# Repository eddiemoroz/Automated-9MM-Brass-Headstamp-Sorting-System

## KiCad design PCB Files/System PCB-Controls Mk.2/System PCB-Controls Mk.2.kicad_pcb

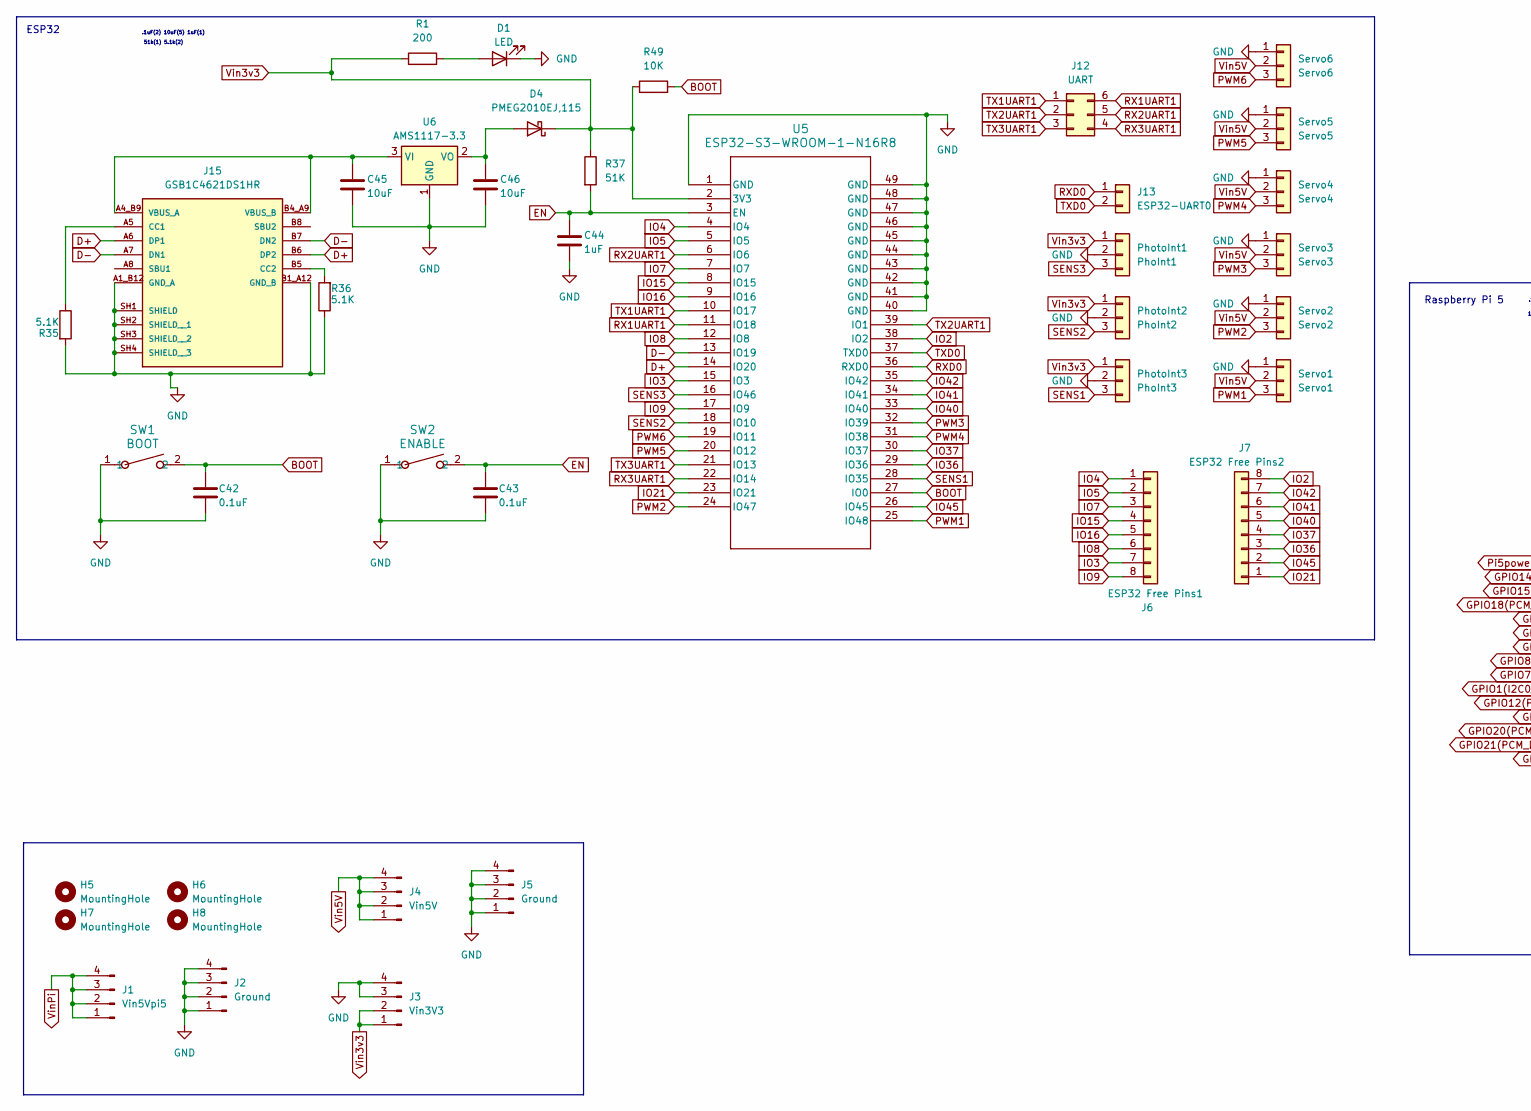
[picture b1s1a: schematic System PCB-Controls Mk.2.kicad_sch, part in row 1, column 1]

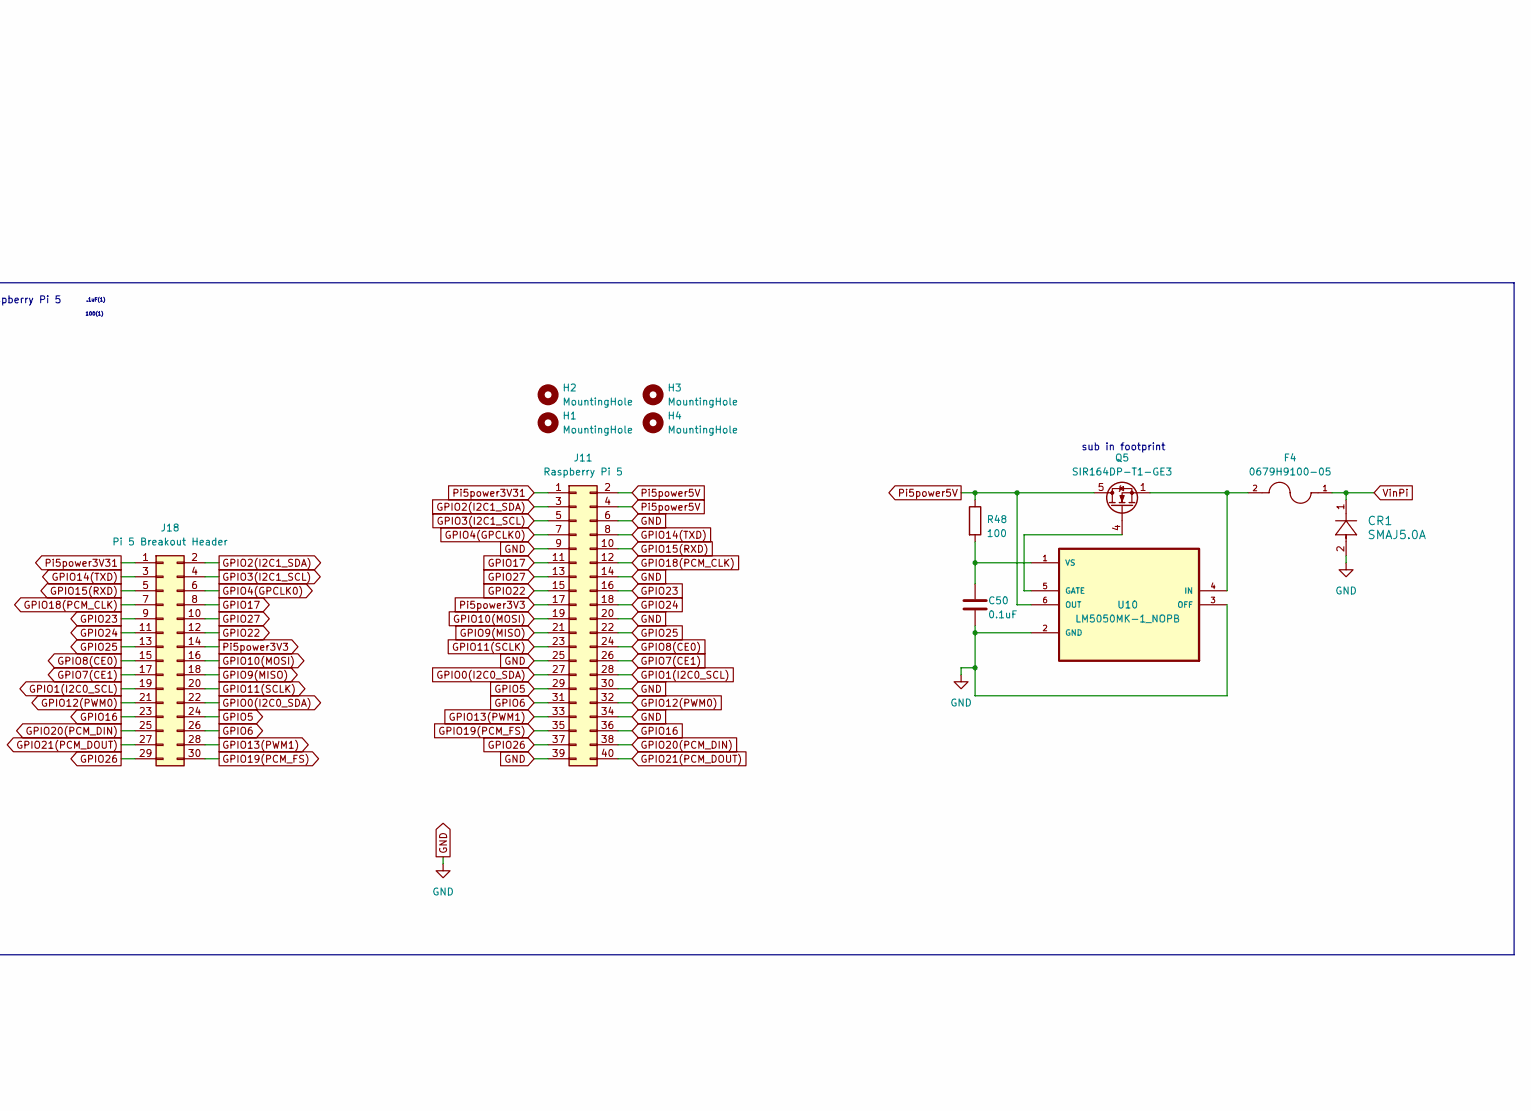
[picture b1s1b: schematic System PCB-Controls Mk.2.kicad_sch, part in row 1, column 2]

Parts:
C42, C43, C50: 0.1uF; C_0805_2012Metric_Pad1.18x1.45mm_HandSolder
C44: 1uF; C_0603_1608Metric_Pad1.08x0.95mm_HandSolder
C45, C46: 10uF; C_1206_3216Metric_Pad1.33x1.80mm_HandSolder
CR1: SMAJ5.0A; SMA5.0A
D1: LED; R_1206_3216Metric_Pad1.30x1.75mm_HandSolder
D4: PMEG2010EJ,115; D_SOD-323F
F4: 0679H9100-05; FUSC6125X279N; PARTREV 0679H Apr2019
H1, H2, H3, H4: MountingHole; MountingHole_2.7mm_M2.5
H5, H6, H7, H8: MountingHole; MountingHole_3.2mm_M3
J1: Vin5Vpi5; FanPinHeader_1x04_P2.54mm_Vertical
J2, J5: Ground; FanPinHeader_1x04_P2.54mm_Vertical
J3: Vin3V3; FanPinHeader_1x04_P2.54mm_Vertical
J4: Vin5V; FanPinHeader_1x04_P2.54mm_Vertical
J6: ESP32 Free Pins1; PinSocket_1x08_P2.54mm_Vertical
J7: ESP32 Free Pins2; PinSocket_1x08_P2.54mm_Vertical
J11: Raspberry Pi 5; PinSocket_2x20_P2.54mm_Vertical
J12: UART; PinSocket_2x03_P2.54mm_Vertical
J13: ESP32-UART0; PinSocket_1x02_P2.54mm_Vertical
J15: GSB1C4621DS1HR; AMPHENOL_GSB1C4621DS1HR; PARTREV AX1
J18: Pi 5 Breakout Header; PinHeader_2x15_P2.54mm_Vertical
PhotoInt1: PhoInt1; FanPinHeader_1x03_P2.54mm_Vertical
PhotoInt2: PhoInt2; FanPinHeader_1x03_P2.54mm_Vertical
PhotoInt3: PhoInt3; FanPinHeader_1x03_P2.54mm_Vertical
Q5: SIR164DP-T1-GE3; PowerPAK_SO-8_Single
R1: 200; R_1206_3216Metric_Pad1.30x1.75mm_HandSolder
R35, R36: 5.1K; R_1206_3216Metric_Pad1.30x1.75mm_HandSolder
R37: 51K; R_1206_3216Metric_Pad1.30x1.75mm_HandSolder
R48: 100; R_1206_3216Metric_Pad1.30x1.75mm_HandSolder
R49: 10K; R_1206_3216Metric_Pad1.30x1.75mm_HandSolder
SW1: BOOT; SW_PTS636_CNK
SW2: ENABLE; SW_PTS636_CNK
Servo1: Servo1; PinSocket_1x03_P2.54mm_Vertical
Servo2: Servo2; PinSocket_1x03_P2.54mm_Vertical
Servo3: Servo3; PinSocket_1x03_P2.54mm_Vertical
Servo4: Servo4; PinSocket_1x03_P2.54mm_Vertical
Servo5: Servo5; PinSocket_1x03_P2.54mm_Vertical
Servo6: Servo6; PinSocket_1x03_P2.54mm_Vertical
U5: ESP32-S3-WROOM-1-N16R8; ESP32-S3-WROOM-1_EXP
U6: AMS1117-3.3; SOT-223-3_TabPin2
U10: LM5050MK-1_NOPB; LM5050MK-1NOPB

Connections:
BOOT: C42.1, R49.2, SW1.2, U5.27 (IO0)
D+: J15.A6 (DP1), J15.B6 (DP2), U5.14 (IO20)
D-: J15.A7 (DN1), J15.B7 (DN2), U5.13 (IO19)
EN: C43.1, C44.1, R37.2, SW2.2, U5.3 (EN)
GND: C42.2, C43.2, C44.2, C45.2, C46.2, C50.2, CR1.2, D1.1 (K), J2.1, J2.2, J2.3, J2.4, J3.3, J3.4, J5.1, J5.2, J5.3, J5.4, J11.6, J11.9, J11.14, J11.20, J11.25, J11.30, J11.34, J11.39, J15.A1_B12 (GND_A), J15.B1_A12 (GND_B), J15.SH1 (SHIELD), J15.SH2 (SHIELD__1), J15.SH3 (SHIELD__2), J15.SH4 (SHIELD__3), PhotoInt1.2, PhotoInt2.2, PhotoInt3.2, R35.2, R36.1, SW1.1, SW2.1, Servo1.1, Servo2.1, Servo3.1, Servo4.1, Servo5.1, Servo6.1, U5.1 (GND), U5.40 (GND), U5.41 (GND), U5.42 (GND), U5.43 (GND), U5.44 (GND), U5.45 (GND), U5.46 (GND), U5.47 (GND), U5.48 (GND), U5.49 (GND), U6.1 (GND), U10.2 (GND), U10.3 (OFF)
GPIO0(I2C0_SDA): J11.27, J18.22
GPIO1(I2C0_SCL): J11.28, J18.19
GPIO2(I2C1_SDA): J11.3, J18.2
GPIO3(I2C1_SCL): J11.5, J18.4
GPIO4(GPCLK0): J11.7, J18.6
GPIO5: J11.29, J18.24
GPIO6: J11.31, J18.26
GPIO7(CE1): J11.26, J18.17
GPIO8(CE0): J11.24, J18.15
GPIO9(MISO): J11.21, J18.18
GPIO10(MOSI): J11.19, J18.16
GPIO11(SCLK): J11.23, J18.20
GPIO12(PWM0): J11.32, J18.21
GPIO13(PWM1): J11.33, J18.28
GPIO14(TXD): J11.8, J18.3
GPIO15(RXD): J11.10, J18.5
GPIO16: J11.36, J18.23
GPIO17: J11.11, J18.8
GPIO18(PCM_CLK): J11.12, J18.7
GPIO19(PCM_FS): J11.35, J18.30
GPIO20(PCM_DIN): J11.38, J18.25
GPIO21(PCM_DOUT): J11.40, J18.27
GPIO22: J11.15, J18.12
GPIO23: J11.16, J18.9
GPIO24: J11.18, J18.11
GPIO25: J11.22, J18.13
GPIO26: J11.37, J18.29
GPIO27: J11.13, J18.10
IO2: J7.8, U5.38 (IO2)
IO3: J6.7, U5.15 (IO3)
IO4: J6.1, U5.4 (IO4)
IO5: J6.2, U5.5 (IO5)
IO7: J6.3, U5.7 (IO7)
IO8: J6.6, U5.12 (IO8)
IO9: J6.8, U5.17 (IO9)
IO15: J6.4, U5.8 (IO15)
IO16: J6.5, U5.9 (IO16)
IO21: J7.1, U5.23 (IO21)
IO36: J7.3, U5.29 (IO36)
IO37: J7.4, U5.30 (IO37)
IO40: J7.5, U5.33 (IO40)
IO41: J7.6, U5.34 (IO41)
IO42: J7.7, U5.35 (IO42)
IO45: J7.2, U5.26 (IO45)
unnamed: D1.2 (A), R1.2
unnamed: C46.1, D4.2 (A), U6.2 (VO)
unnamed: J15.A5 (CC1), R35.1
unnamed: J15.B5 (CC2), R36.2
unnamed: C45.1, J15.A4_B9 (VBUS_A), J15.B4_A9 (VBUS_B), U6.3 (VI)
unnamed: Q5.4 (G), U10.5 (GATE)
unnamed: F4.2, Q5.1 (S), Q5.2 (S), Q5.3 (S), U10.4 (IN)
unnamed: C50.1, R48.2, U10.1 (VS)
PWM1: Servo1.3, U5.25 (IO48)
PWM2: Servo2.3, U5.24 (IO47)
PWM3: Servo3.3, U5.32 (IO39)
PWM4: Servo4.3, U5.31 (IO38)
PWM5: Servo5.3, U5.20 (IO12)
PWM6: Servo6.3, U5.19 (IO11)
Pi5power3V3: J11.17, J18.14
Pi5power3V31: J11.1, J18.1
Pi5power5V: J11.2, J11.4, Q5.5 (D), R48.1, U10.6 (OUT)
RX1UART1: J12.6, U5.11 (IO18)
RX2UART1: J12.5, U5.6 (IO6)
RX3UART1: J12.4, U5.22 (IO14)
RXD0: J13.1, U5.36 (RXD0)
SENS1: PhotoInt3.3, U5.28 (IO35)
SENS2: PhotoInt2.3, U5.18 (IO10)
SENS3: PhotoInt1.3, U5.16 (IO46)
TX1UART1: J12.1, U5.10 (IO17)
TX2UART1: J12.2, U5.39 (IO1)
TX3UART1: J12.3, U5.21 (IO13)
TXD0: J13.2, U5.37 (TXD0)
Vin3v3: D4.1 (K), J3.1, J3.2, PhotoInt1.1, PhotoInt2.1, PhotoInt3.1, R1.1, R37.1, R49.1, U5.2 (3V3)
Vin5V: J4.1, J4.2, J4.3, J4.4, Servo1.2, Servo2.2, Servo3.2, Servo4.2, Servo5.2, Servo6.2
VinPi: CR1.1, F4.1, J1.1, J1.2, J1.3, J1.4

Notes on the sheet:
sub in footprint
.1uF(2) 10uF(5) 1uF(1)
.1uF(1)
ESP32
100(1)
Raspberry Pi 5
51k(1) 5.1k(2)

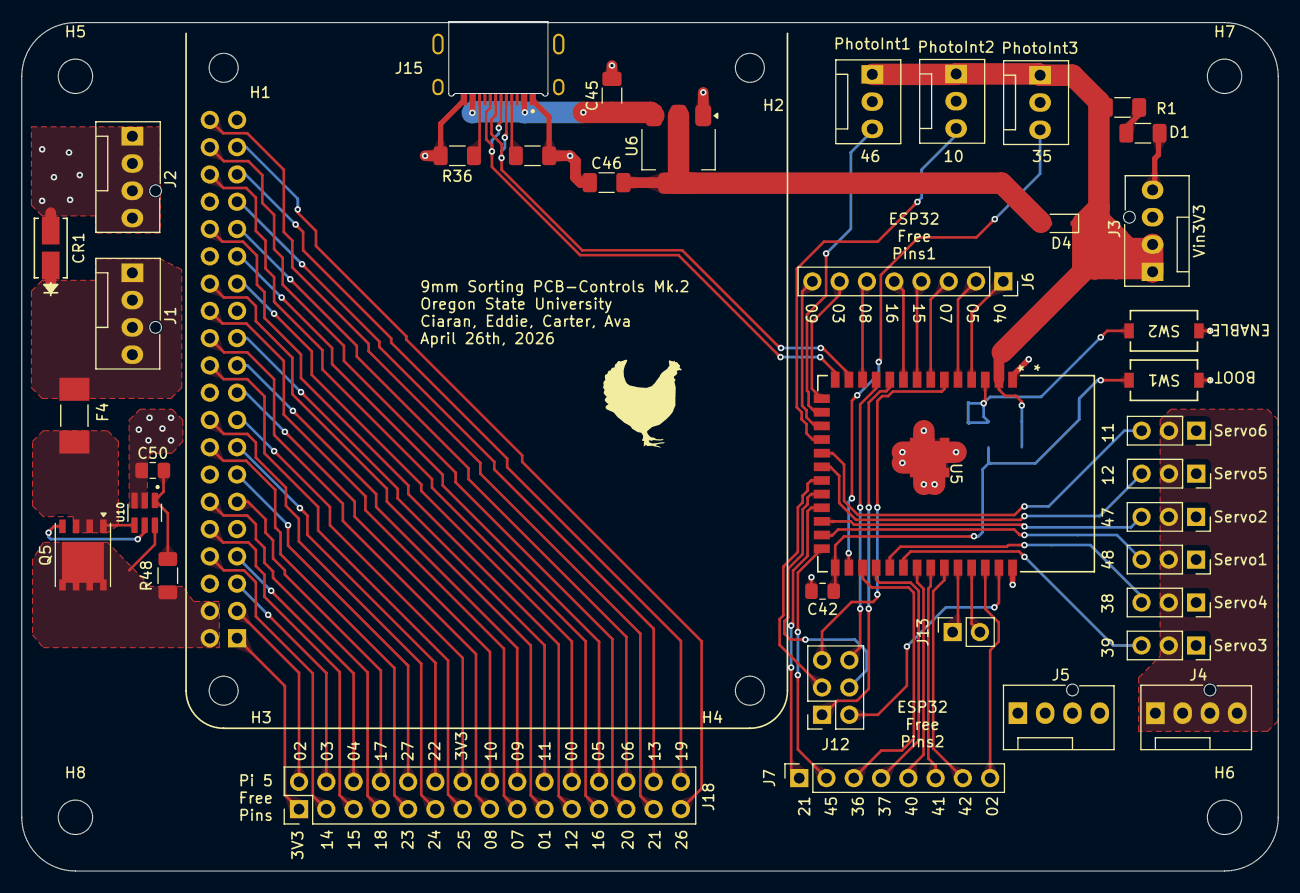
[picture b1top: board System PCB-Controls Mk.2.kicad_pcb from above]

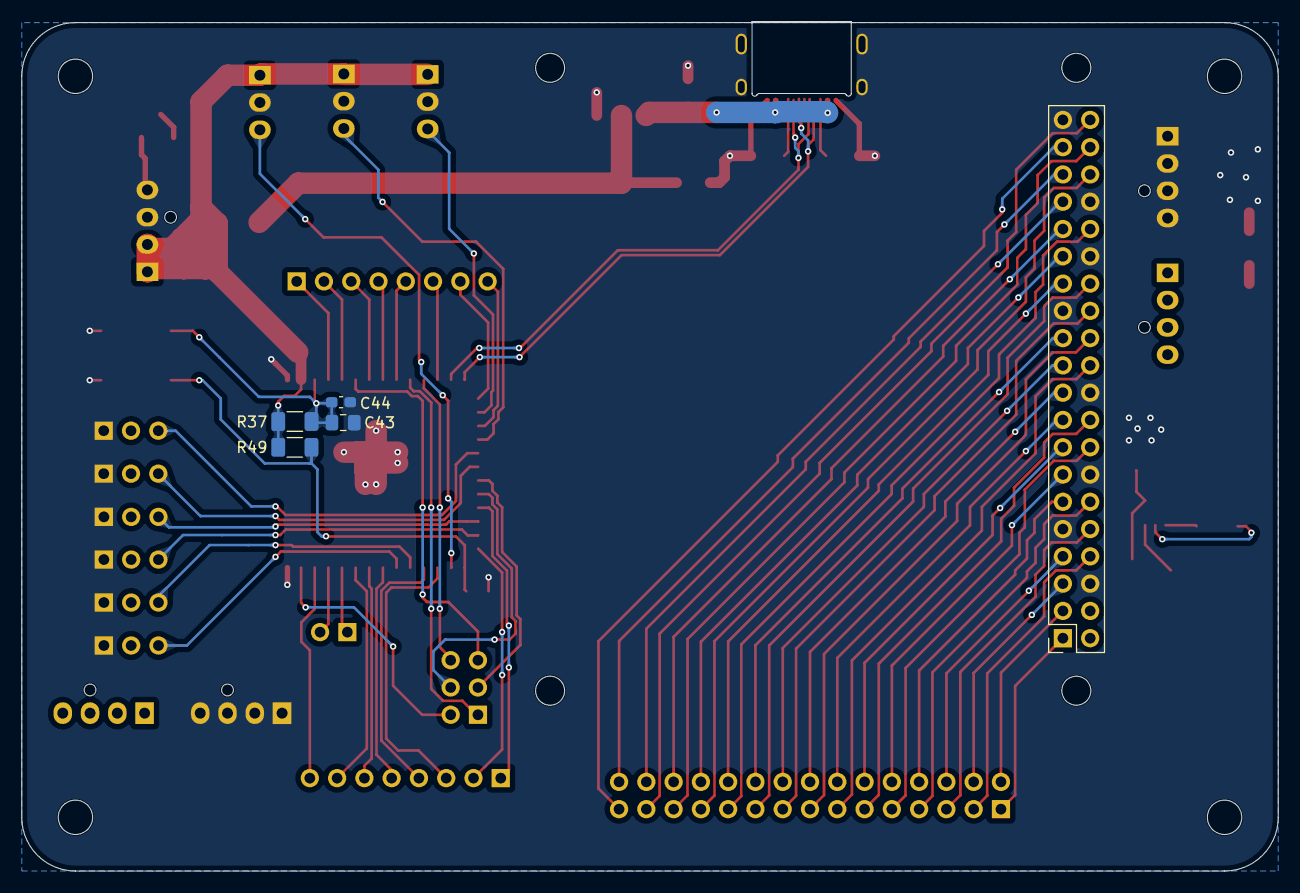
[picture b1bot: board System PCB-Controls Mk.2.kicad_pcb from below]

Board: 2 copper layers, 117.0 x 79.1 mm, 51 parts (5 on the bottom side), 80 nets.

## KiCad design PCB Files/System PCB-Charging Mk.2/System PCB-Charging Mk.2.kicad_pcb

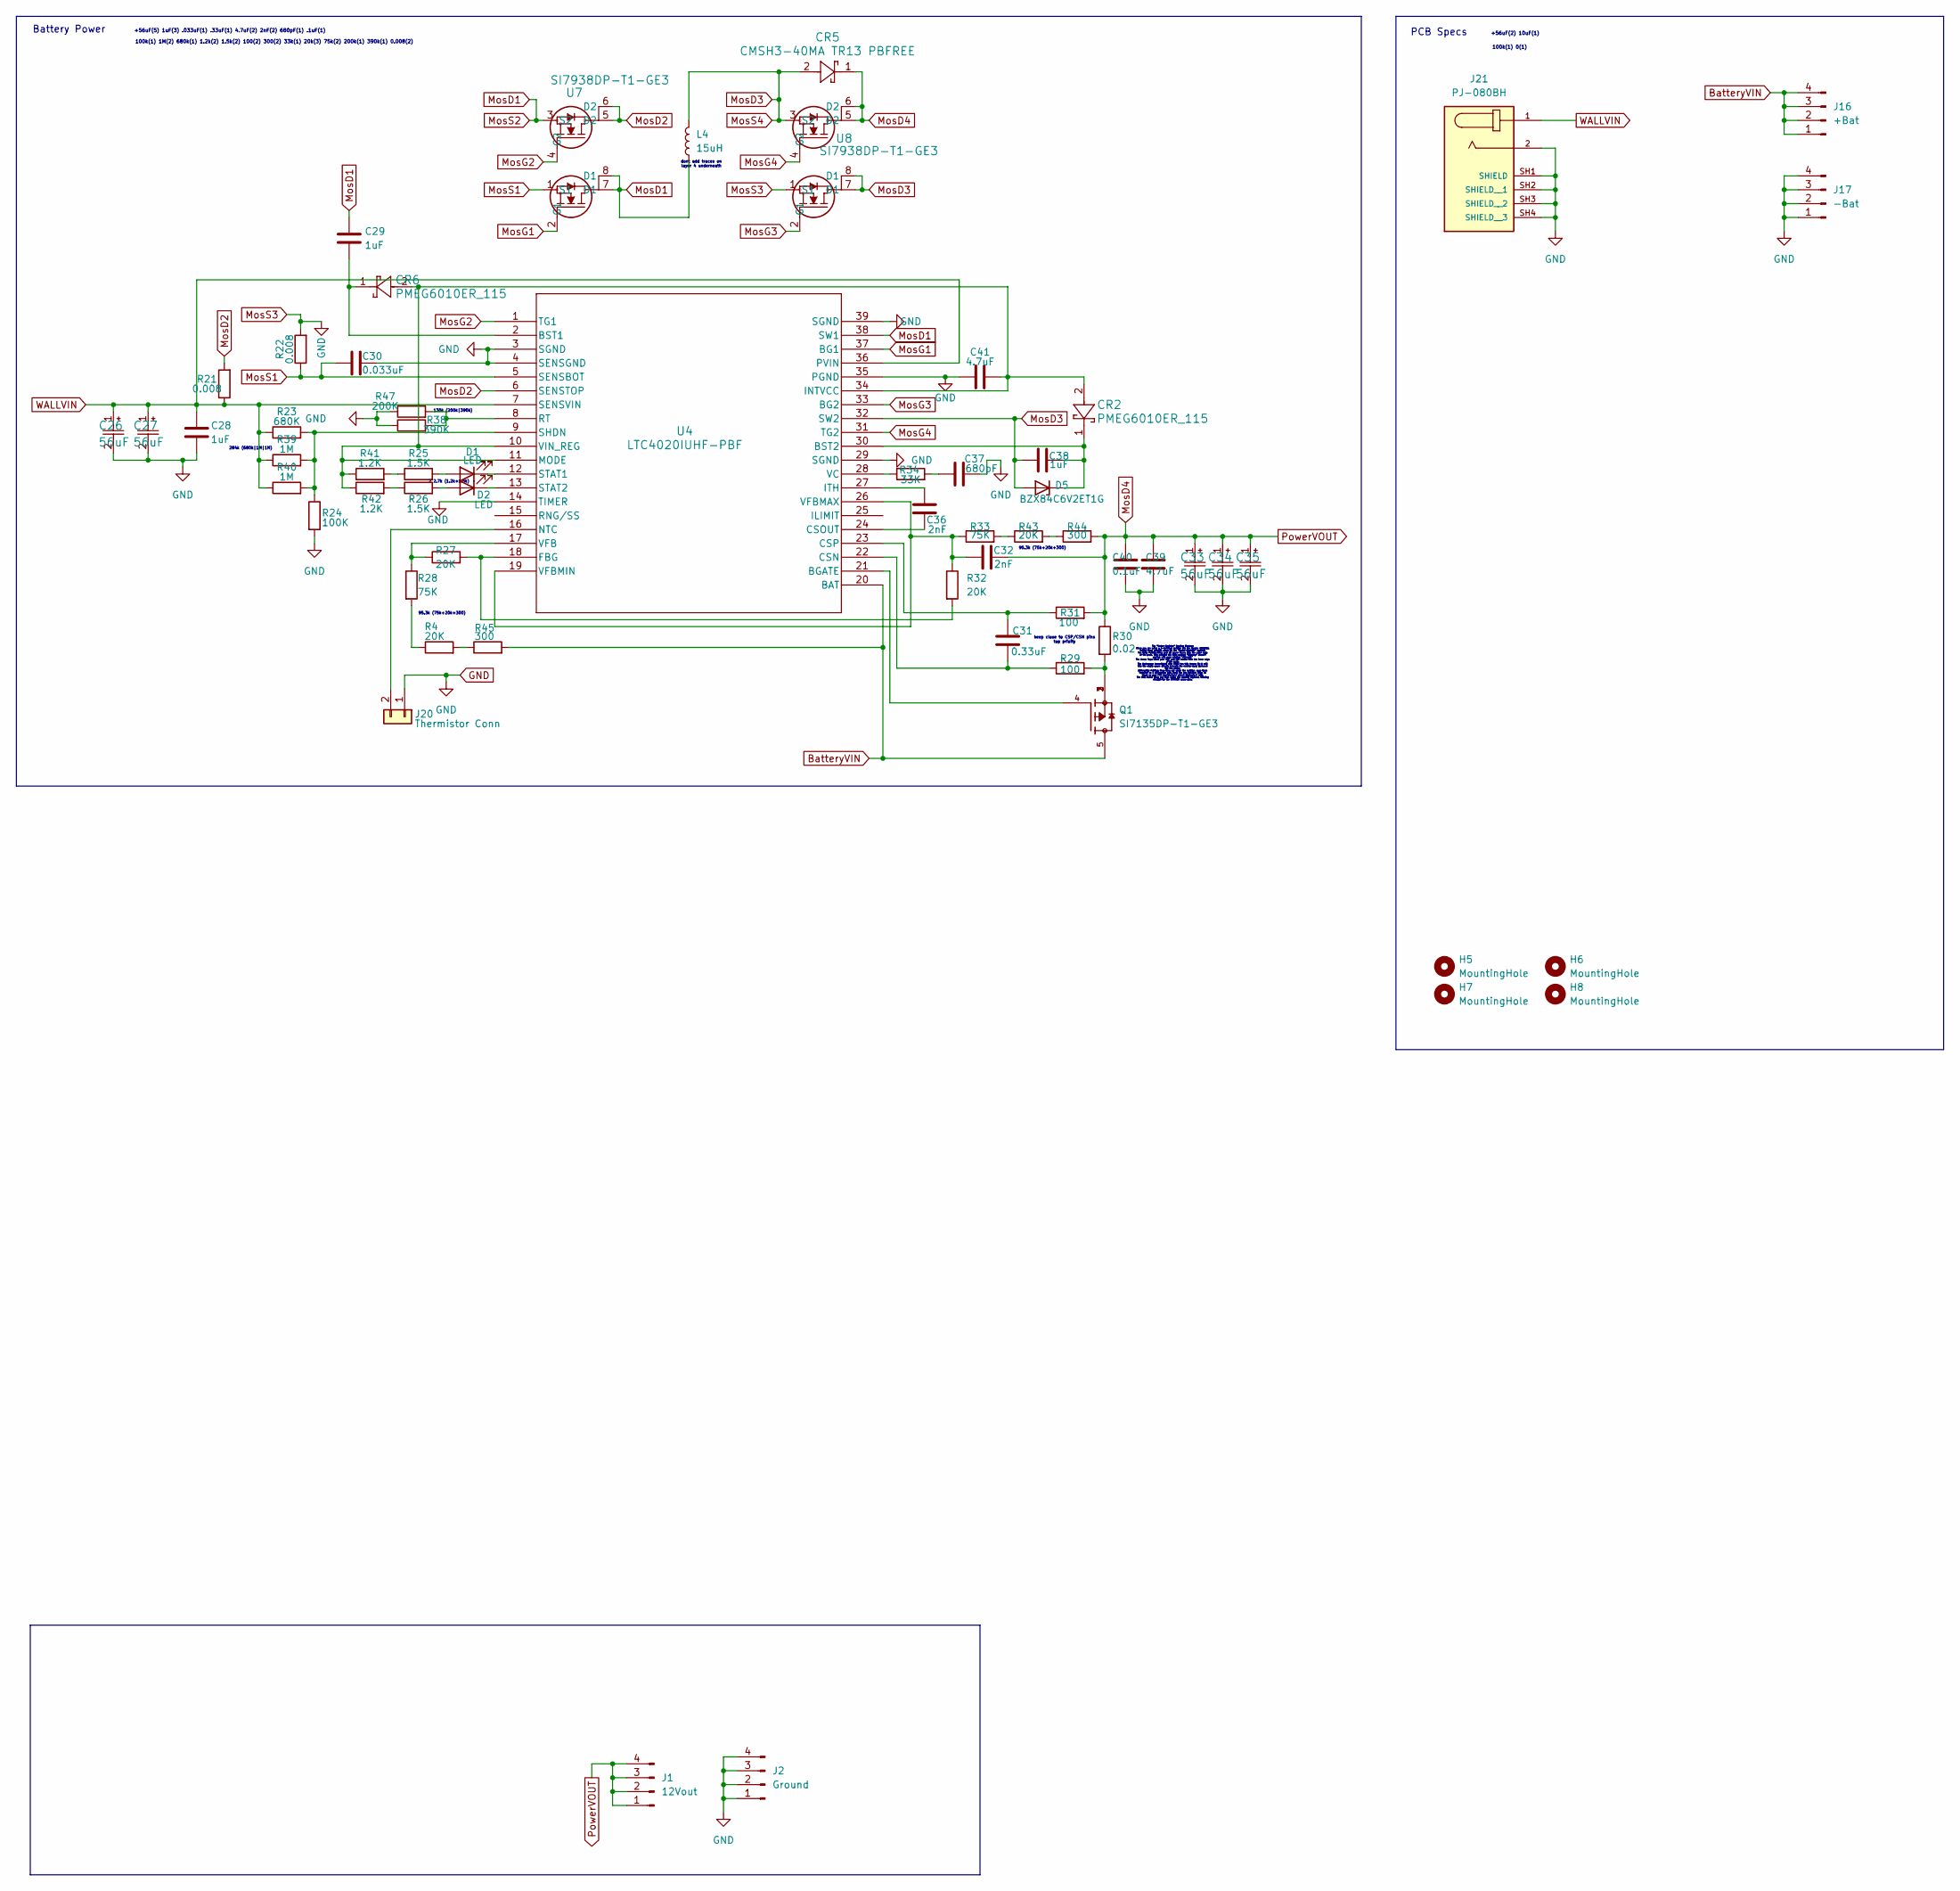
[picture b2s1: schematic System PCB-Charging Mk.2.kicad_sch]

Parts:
C26, C27, C33, C34, C35: 56uF; CAP_GY_6P3X5P8_NCH-M
C28, C29, C38: 1uF; C_0603_1608Metric_Pad1.08x0.95mm_HandSolder
C30: 0.033uF; C_0805_2012Metric_Pad1.18x1.45mm_HandSolder
C31: 0.33uF; C_0805_2012Metric_Pad1.18x1.45mm_HandSolder
C32, C36: 2nF; C_0805_2012Metric_Pad1.18x1.45mm_HandSolder
C37: 680pF; C_0603_1608Metric_Pad1.08x0.95mm_HandSolder
C39, C41: 4.7uF; C_1206_3216Metric_Pad1.33x1.80mm_HandSolder
C40: 0.1uF; C_0805_2012Metric_Pad1.18x1.45mm_HandSolder
CR2, CR6: PMEG6010ER_115; Nexperia_CFP3_SOD-123W
CR5: CMSH3-40MA TR13 PBFREE; CR_SMA-CMSH3-40MA_CNS-M
D1, D2: LED; LED_0201_0603Metric_Pad0.64x0.40mm_HandSolder
D5: BZX84C6V2ET1G; SOT-23_Handsoldering
H5, H6, H7, H8: MountingHole; MountingHole_3.2mm_M3
J1: 12Vout; FanPinHeader_1x04_P2.54mm_Vertical
J2: Ground; FanPinHeader_1x04_P2.54mm_Vertical
J16: +Bat; FanPinHeader_1x04_P2.54mm_Vertical
J17: -Bat; FanPinHeader_1x04_P2.54mm_Vertical
J20: Thermistor Conn; PinSocket_1x02_P2.54mm_Vertical
J21: PJ-080BH; CUI_PJ-080BH; PARTREV 1.04
L4: 15uH; IND_SRP1265A-150M
Q1: SI7135DP-T1-GE3; TRANS_SI7135DP-T1-GE3; PARTREV A
R4, R27, R32, R43: 20K; R_1206_3216Metric_Pad1.30x1.75mm_HandSolder
R21, R22: 0.008; R_2512_6332Metric_Pad1.40x3.35mm_HandSolder
R23: 680K; R_1206_3216Metric_Pad1.30x1.75mm_HandSolder
R24: 100K; R_1206_3216Metric_Pad1.30x1.75mm_HandSolder
R25, R26: 1.5K; R_1206_3216Metric_Pad1.30x1.75mm_HandSolder
R28, R33: 75K; R_1206_3216Metric_Pad1.30x1.75mm_HandSolder
R29, R31: 100; R_1206_3216Metric_Pad1.30x1.75mm_HandSolder
R30: 0.02; R_2512_6332Metric_Pad1.40x3.35mm_HandSolder
R34: 33K; R_1206_3216Metric_Pad1.30x1.75mm_HandSolder
R38: 390K; R_1206_3216Metric_Pad1.30x1.75mm_HandSolder
R39, R40: 1M; R_1206_3216Metric_Pad1.30x1.75mm_HandSolder
R41, R42: 1.2K; R_1206_3216Metric_Pad1.30x1.75mm_HandSolder
R44, R45: 300; R_1206_3216Metric_Pad1.30x1.75mm_HandSolder
R47: 200K; R_1206_3216Metric_Pad1.30x1.75mm_HandSolder
U4: LTC4020IUHF-PBF; LTC4020IUHF#PBF
U7, U8: SI7938DP-T1-GE3; PowerPAK_DP-T1-GE3_VIS

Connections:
BatteryVIN: J16.1, J16.2, J16.3, J16.4, Q1.5, R45.2, U4.20 (BAT)
GND: C26.2, C27.2, C28.2, C30.1, C33.2, C34.2, C35.2, C37.2, C39.2, C40.2, C41.1, J2.1, J2.2, J2.3, J2.4, J17.1, J17.2, J17.3, J17.4, J20.1, J21.2, J21.SH1 (SHIELD), J21.SH2 (SHIELD__1), J21.SH3 (SHIELD__2), J21.SH4 (SHIELD__3), R22.2, R24.2, R38.1, R47.1, U4.3 (SGND), U4.4 (SENSGND), U4.14 (TIMER), U4.29 (SGND), U4.35 (PGND), U4.39 (SGND), U8.1 (S1)
MosD1: C29.1, L4.1, U4.38 (SW1), U7.3 (S2), U7.7 (D1), U7.8 (D1)
MosD2: R21.2, U4.6 (SENSTOP), U7.5 (D2), U7.6 (D2)
MosD3: C38.1, CR5.2, D5.1 (A), L4.2, U4.32 (SW2), U8.3 (S2), U8.7 (D1), U8.8 (D1)
MosD4: C32.2, C33.1, C34.1, C35.1, C39.1, C40.1, CR5.1, J1.1, J1.2, J1.3, J1.4, R30.1, R31.2, R44.2, U8.5 (D2), U8.6 (D2)
MosG1: U4.37 (BG1), U7.2 (G1)
MosG2: U4.1 (TG1), U7.4 (G2)
MosG3: U4.33 (BG2), U8.2 (G1)
MosG4: U4.31 (TG2), U8.4 (G2)
MosS1: C30.2, R22.1, U4.5 (SENSBOT), U7.1 (S1)
unnamed: C37.1, R34.2
unnamed: D1.2 (A), R25.2
unnamed: D1.1 (K), U4.12 (STAT1)
unnamed: D2.2 (A), R26.2
unnamed: D2.1 (K), U4.13 (STAT2)
unnamed: C38.2, CR2.1, D5.3 (K), U4.30 (BST2)
unnamed: J20.2, U4.16 (NTC)
unnamed: Q1.1, Q1.2, Q1.3, R29.2, R30.2
unnamed: R4.2, R45.1
unnamed: R25.1, R41.2
unnamed: R26.1, R42.2
unnamed: R4.1, R28.2
unnamed: R33.2, R43.1
unnamed: R43.2, R44.1
unnamed: Q1.4, U4.21 (BGATE)
unnamed: C29.2, CR6.1, U4.2 (BST1)
unnamed: C31.2, R29.1, U4.22 (CSN)
unnamed: C36.2, U4.24 (CSOUT)
unnamed: C31.1, R31.1, U4.23 (CSP)
unnamed: R27.2, R32.2, U4.18 (FBG)
unnamed: C41.2, CR2.2, CR6.2, R41.1, R42.1, U4.10 (VIN_REG), U4.11 (MODE), U4.34 (INTVCC)
unnamed: C36.1, U4.27 (ITH)
unnamed: R38.2, R47.2, U4.8 (RT)
unnamed: R23.2, R24.1, R39.2, R40.2, U4.9 (SHDN)
unnamed: R34.1, U4.28 (VC)
unnamed: R27.1, R28.1, U4.17 (VFB)
unnamed: C32.1, R32.1, R33.1, U4.19 (VFBMIN), U4.26 (VFBMAX)
WALLVIN: C26.1, C27.1, C28.1, J21.1, R21.1, R23.1, R39.1, R40.1, U4.7 (SENSVIN), U4.36 (PVIN)

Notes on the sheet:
95.3k (75k+20k+300)
2 2.7k (1.2k+1.5k)
284k (680k|1M|1M)
+56uF(5) 1uF(3) .033uF(1) .33uF(1) 4.7uF(2) 2nF(2) 680pF(1) .1uF(1)
+56uF(2) 10uF(1)
PCB Specs
130k (200k|390k)
100k(1) 1M(2) 680k(1) 1.2k(2) 1.5k(2) 100(2) 300(2) 33k(1) 20k(3) 75k(2) 200k(1) 390k(1) 0.008(2)
keep close to CSP/CSN pins top prioity
dont add traces on layer 4 underneath
Battery Power
100k(1) 0(1)
The "Under-Resistor" Routing Strategy Since you are using a 2-terminal resistor like the Bourns CRA2512, follow these specific steps for the "Under-Resistor" method: The Entry Points: Bring your 8A power traces into the outer ends of the pads. This ensures the high-current "highway" doesn't overlap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

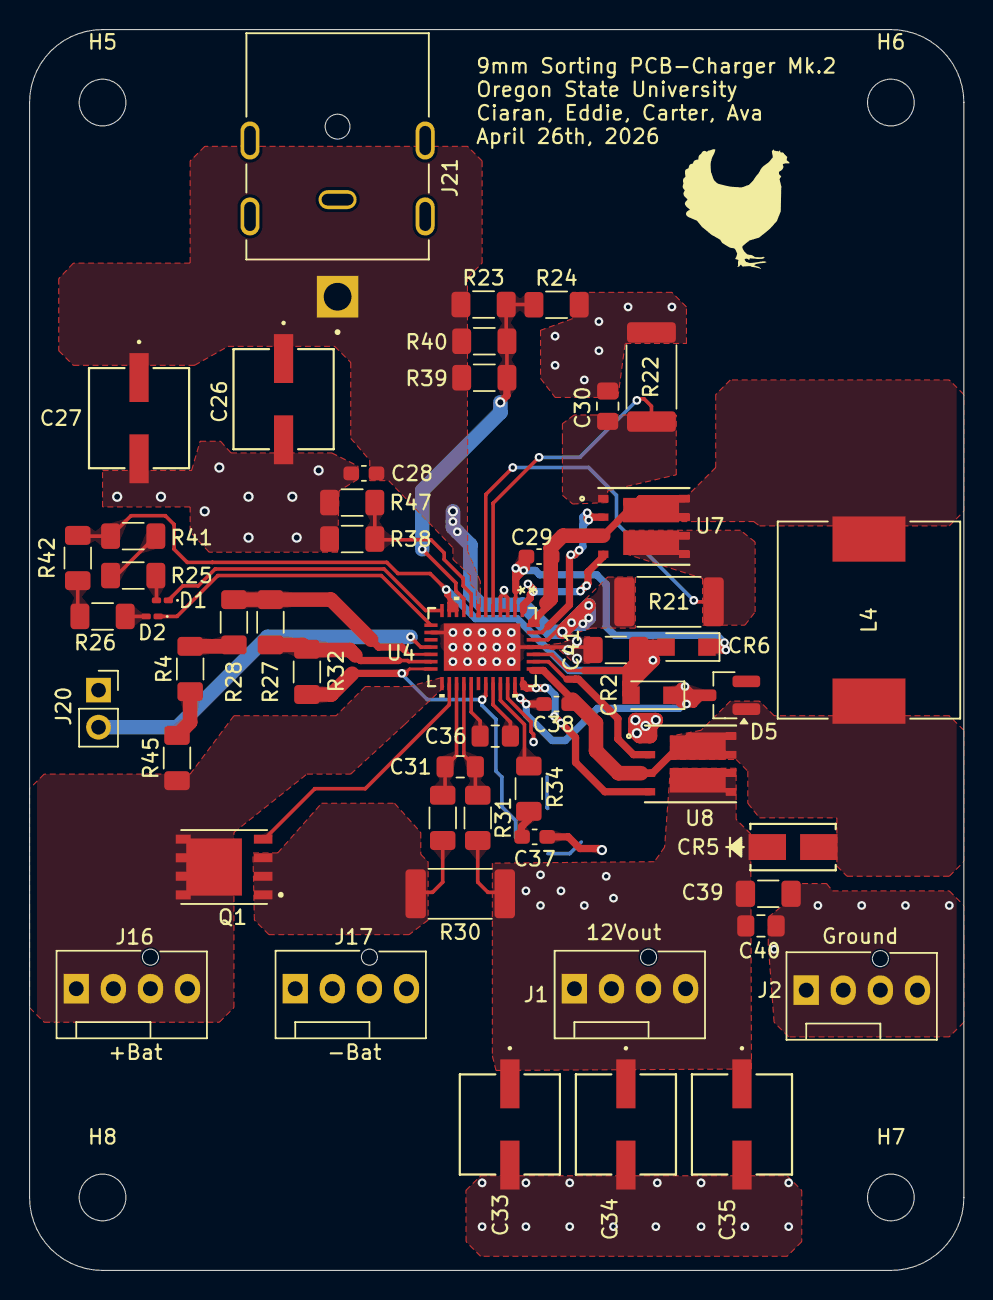
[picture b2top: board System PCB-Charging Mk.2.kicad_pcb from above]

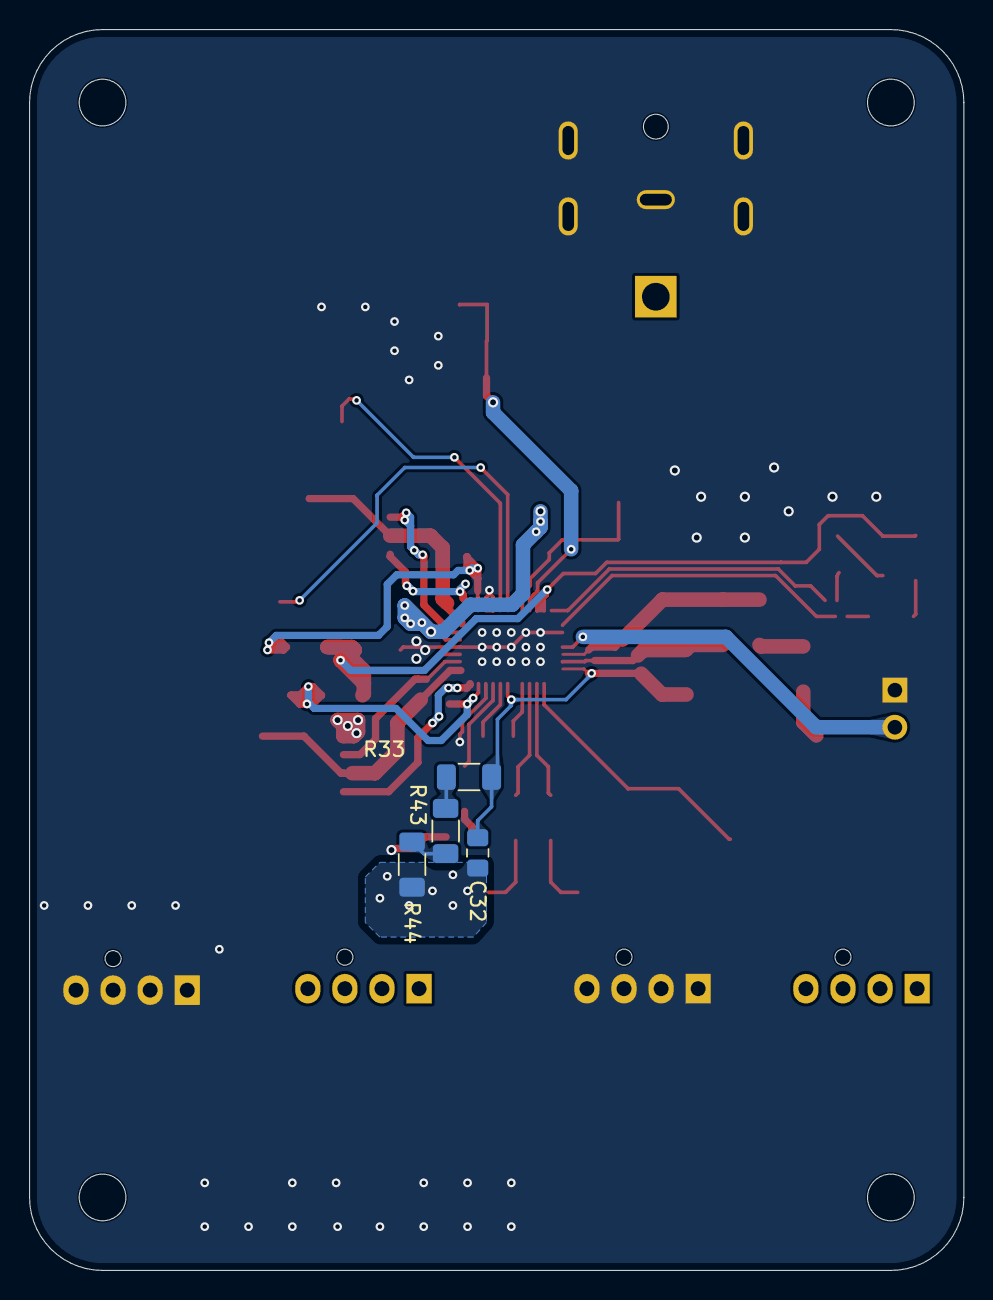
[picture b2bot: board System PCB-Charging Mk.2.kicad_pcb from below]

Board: 2 copper layers, 64.0 x 85.0 mm, 61 parts (4 on the bottom side), 39 nets.
